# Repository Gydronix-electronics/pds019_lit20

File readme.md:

# PDS019_lit20

В этом репозитории содержатся исходники устройства PDS019_lit20.

Конструктивно устройство представляет из себя две печатные платы, размещенные в корпусе для монтажа на DIN-рейку [GAINTA D3MG](https://www.gainta.com/en/d3mg.html)

# Внешний вид платы А (верхней платы)

# Внешний вид платы B (нижней платы)

3d модель для онлайн просмотра доступна [по ссылке](https://a360.co/4tmWj8G)

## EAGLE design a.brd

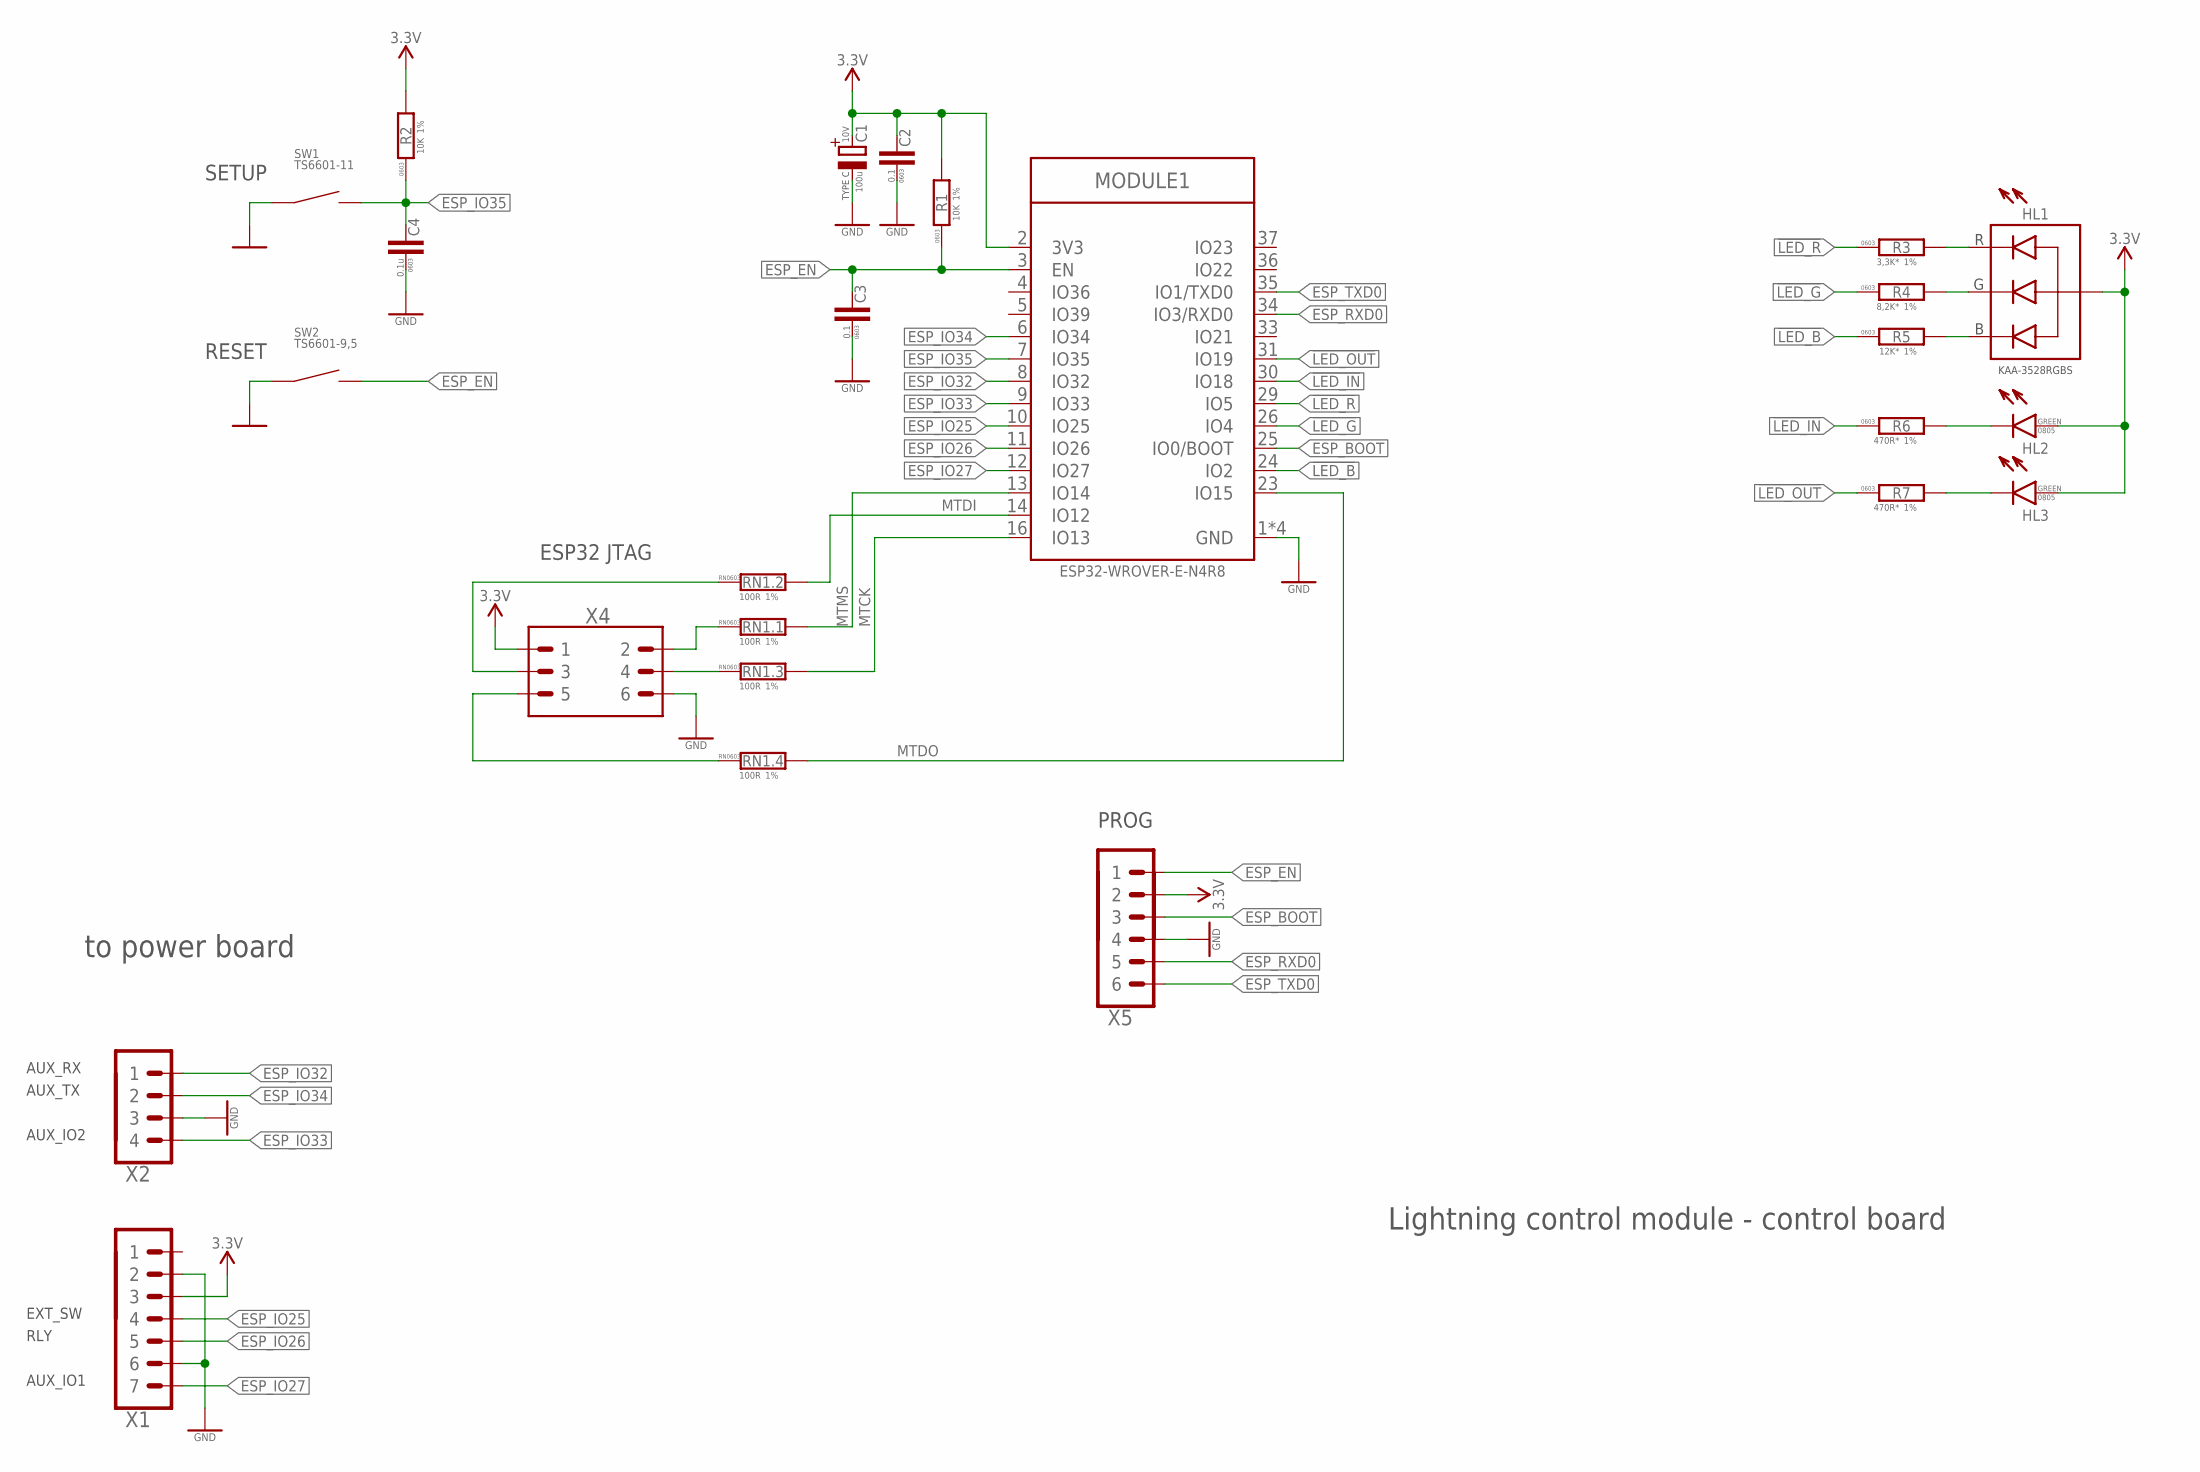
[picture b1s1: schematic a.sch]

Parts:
C1: 100u; CTANT_TYPE_C; VOLTAGE 10V
C2, C3: 0.1; C0603
C4: 0.1u; C0603
HL1: LED_RGB-KAA-3528RGBS; LED3528
HL2, HL3: LED-0805; LED0805
MODULE1: ESP32-WROVER-(I)E; ESP32-WROVER-E
R1, R2: 10K; R0603
R3: 3,3K*; R0603
R4: 8,2K*; R0603
R5: 12K*; R0603
R6, R7: 470R*; R0603
RN1: 100R; R_4X0603
SW1: TS6601-11; SW4-6.0X6.0X5.0MM
SW2: TS6601-9,5; SW4-6.0X6.0X5.0MM
X1: PINHEAD_1X07-2.54; 1X07-PTH-2.54
X2: PINHEAD_1X04-2.54; 1X04-PTH-2.54
X4: PINHEAD_2X03-PTH-2.54; 2X03-PTH-2.54
X5: PINHEAD_1X06-2-MALE; 1X06-PTH-2

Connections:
!LED_B: MODULE1.24 (IO2), R5.1
!LED_G: MODULE1.26 (IO4), R4.1
!LED_IN: MODULE1.30 (IO18), R6.1
!LED_OUT: MODULE1.31 (IO19), R7.1
!LED_R: MODULE1.29 (IO5), R3.1
ESP_BOOT: MODULE1.25 (IO0/BOOT), X5.3
ESP_EN: C3.2, MODULE1.3 (EN), R1.1, SW2.2, SW2.3 (2), X5.1
ESP_IO25: MODULE1.10 (IO25), X1.4
ESP_IO26: MODULE1.11 (IO26), X1.5
ESP_IO27: MODULE1.12 (IO27), X1.7
ESP_IO32: MODULE1.8 (IO32), X2.1
ESP_IO33: MODULE1.9 (IO33), X2.4
ESP_IO34: MODULE1.6 (IO34), X2.2
ESP_IO35: C4.2, MODULE1.7 (IO35), R2.1, SW1.2, SW1.3 (2)
ESP_RXD0: MODULE1.34 (IO3/RXD0), X5.5
ESP_TXD0: MODULE1.35 (IO1/TXD0), X5.6
GND: C1.-, C2.1, C3.1, C4.1, MODULE1.1 (GND), MODULE1.15 (GND), MODULE1.38 (GND), MODULE1.39 (GND), SW1.1, SW1.4 (1), SW2.1, SW2.4 (1), X1.2, X1.6, X2.3, X4.6, X5.4
MTCK: MODULE1.16 (IO13), RN1.6 (2)
MTDI: MODULE1.14 (IO12), RN1.7 (2)
MTDO: MODULE1.23 (IO15), RN1.5 (2)
MTMS: MODULE1.13 (IO14), RN1.8 (2)
unnamed: HL1.4 (B), R5.2
unnamed: HL1.3 (G), R4.2
unnamed: HL1.1 (R), R3.2
unnamed: HL2.C, R6.2
unnamed: HL3.C, R7.2
unnamed: RN1.4 (1), X4.5
unnamed: RN1.1, X4.2
unnamed: RN1.2 (1), X4.3
unnamed: RN1.3 (1), X4.4
VDD_3V3: C1.+, C2.2, HL1.2 (A), HL2.A, HL3.A, MODULE1.2 (3V3), R1.2, R2.2, X1.3, X4.1, X5.2

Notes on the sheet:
ESP32 JTAG
RESET
SETUP
PROG
to power board
AUX_RX
AUX_TX
AUX_IO2
EXT_SW
RLY
AUX_IO1
Lightning control module - control board

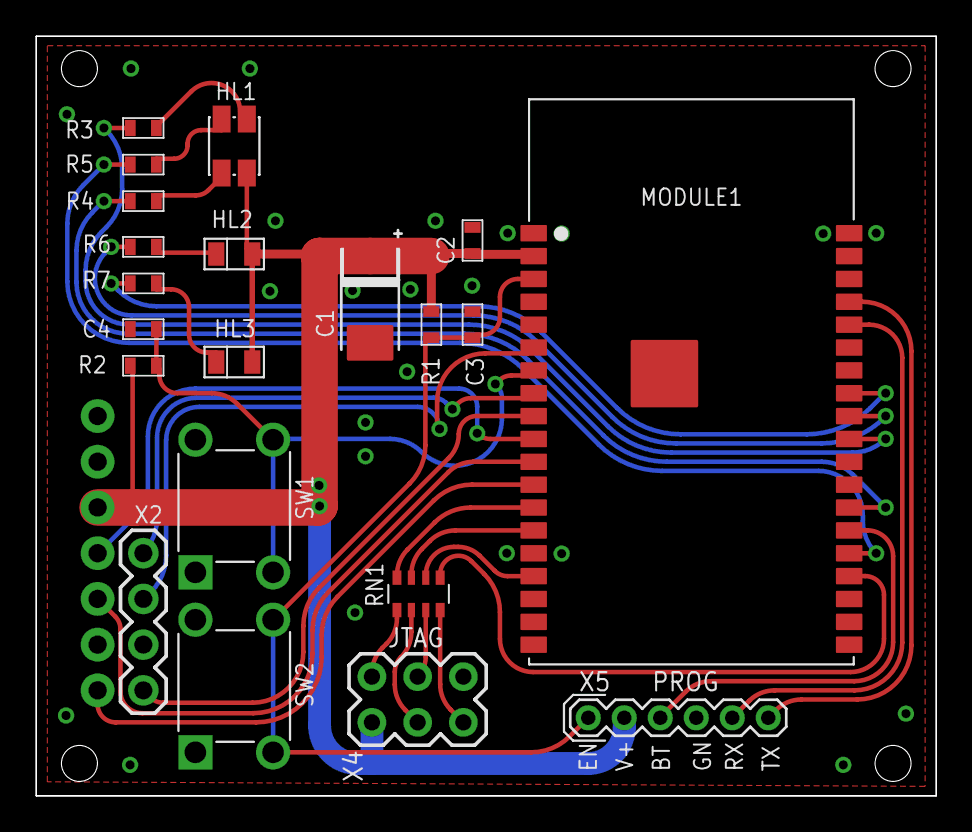
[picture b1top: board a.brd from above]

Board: 2 copper layers, 50.0 x 42.2 mm, 23 parts (1 on the bottom side), 31 nets.

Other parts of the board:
U$2: D3MG_PCB_UP

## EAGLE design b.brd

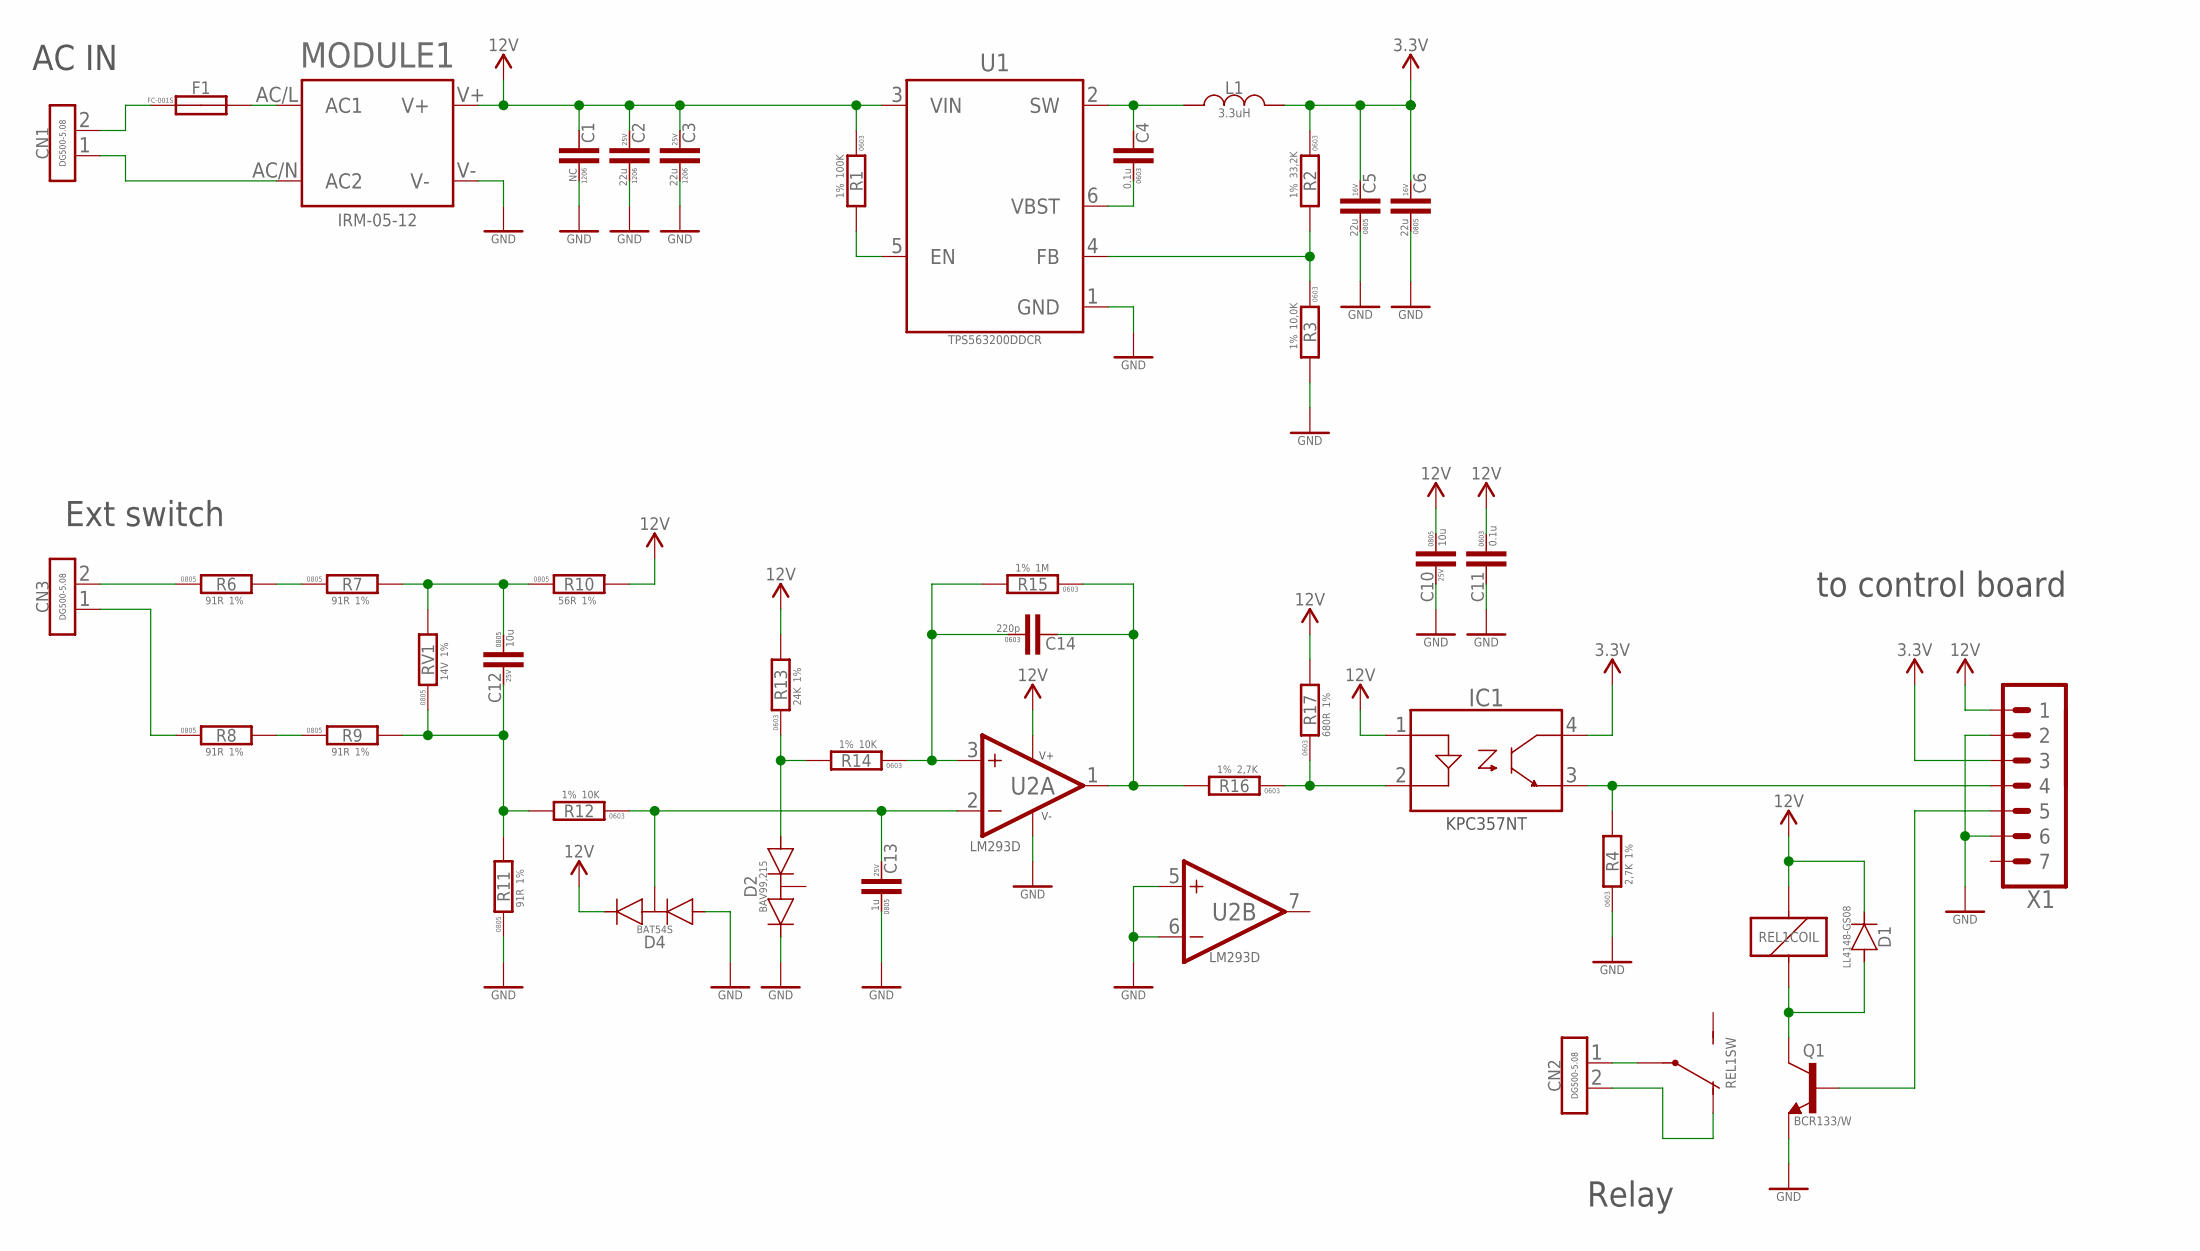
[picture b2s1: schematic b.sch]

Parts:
C1: NC; C1206
C2, C3: 22u; C1206; VOLTAGE 25V
C4, C11: 0.1u; C0603
C5, C6: 22u; C0805; VOLTAGE 16V
C10, C12: 10u; C0805; VOLTAGE 25V
C13: 1u; C0805; VOLTAGE 25V
C14: 220p; C0603
CN1, CN3: DG508V-2P; DG500-5.08-02P
CN2: CON-2P-DG500-5.08; DG500-5.08-02P
D1: LL4148; LL-34
D2: BAV99-SOT23; SOT23
D4: BAT54S-SOT23; SOT23
F1: 2A; FC-001S
IC1: KPC357NT-SOP-4; -SOP-4
L1: 3.3uH; LSMD_05020
MODULE1: IRM-05-12; IRM-05
Q1: BCR133; SOT23B-3
R1: 100K; R0603
R2: 33,2K; R0603
R3: 10,0K; R0603
R4, R16: 2,7K; R0603
R6, R7, R8, R9, R11: 91R; R0805
R10: 56R; R0805
R12, R14: 10K; R0603
R13: 24K; R0603
R15: 1M; R0603
R17: 680R; R0603
REL1: RELAY_SPDTHJR-3FF-SH; HJR-3FF-12VDC-S-Z
RV1: 14V; R0805
U1: TPS563200; SOT23-6
U2: LM293D; SOIC8
X1: PINHEAD_1X07-2.54; 1X07-PTH-2.54

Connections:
EXT_SW: IC1.3 (EMITTER), R4.2, X1.4
GND: C1.P$1 (1), C2.P$1 (1), C3.P$1 (1), C5.1, C6.1, C10.2, C11.2, C13.1, D2.2 (C), D4.1 (A), MODULE1.V-, Q1.2 (E), R3.2, R4.1, R11.1, U1.1 (GND), U2.4 (V-), U2.5 (IN+), U2.6 (IN-), X1.2, X1.6
unnamed: D1.A, Q1.3 (C), REL1.2 (1)
unnamed: Q1.1 (B), X1.5
unnamed: CN2.1, REL1.1 (COM)
unnamed: CN1.1, MODULE1.AC/N (AC2)
unnamed: CN1.2, F1.1-1 (1), F1.1-2 (1)
unnamed: F1.2-1 (2), F1.2-2 (2), MODULE1.AC/L (AC1)
unnamed: CN2.2, REL1.4 (NC)
unnamed: R2.2, R3.1, U1.4 (FB)
unnamed: CN3.2, R6.1
unnamed: CN3.1, R8.1
unnamed: R1.2, U1.5 (EN)
unnamed: C4.1, U1.6 (VBST)
unnamed: C4.2, L1.1, U1.2 (SW)
unnamed: IC1.2 (C), R16.1, R17.1
unnamed: C14.2, R15.1, R16.2, U2.1 (OUT)
unnamed: C13.2, D4.3 (COMMON), R12.1, U2.2 (IN-)
unnamed: C12.1, R7.2, R10.1, RV1.2
unnamed: R6.2, R7.1
unnamed: R8.2, R9.1
unnamed: C14.1, R14.1, R15.2, U2.3 (IN+)
unnamed: D2.1 (A), R13.1, R14.2
unnamed: C12.2, R9.2, R11.2, R12.2, RV1.1
VDD_3V3: C5.2, C6.2, IC1.4 (COLLECTOR), L1.2, R2.1, X1.3
VDD_12V: C1.P$2 (2), C2.P$2 (2), C3.P$2 (2), C10.1, C11.1, D1.C, D4.2 (C), IC1.1 (A), MODULE1.V+, R1.1, R10.2, R13.2, R17.2, REL1.5 (2), U1.3 (VIN), U2.8 (V+), X1.1

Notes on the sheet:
Ext switch
AC IN
Relay
to control board

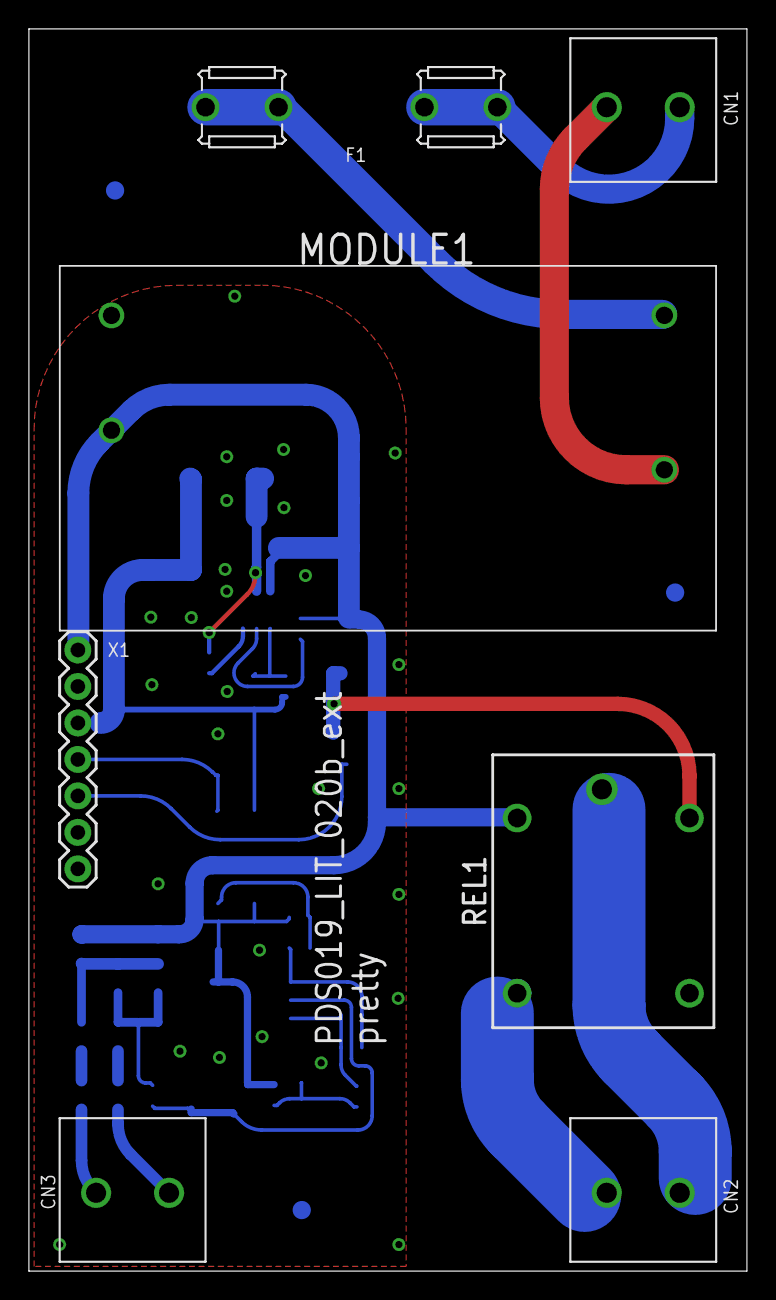
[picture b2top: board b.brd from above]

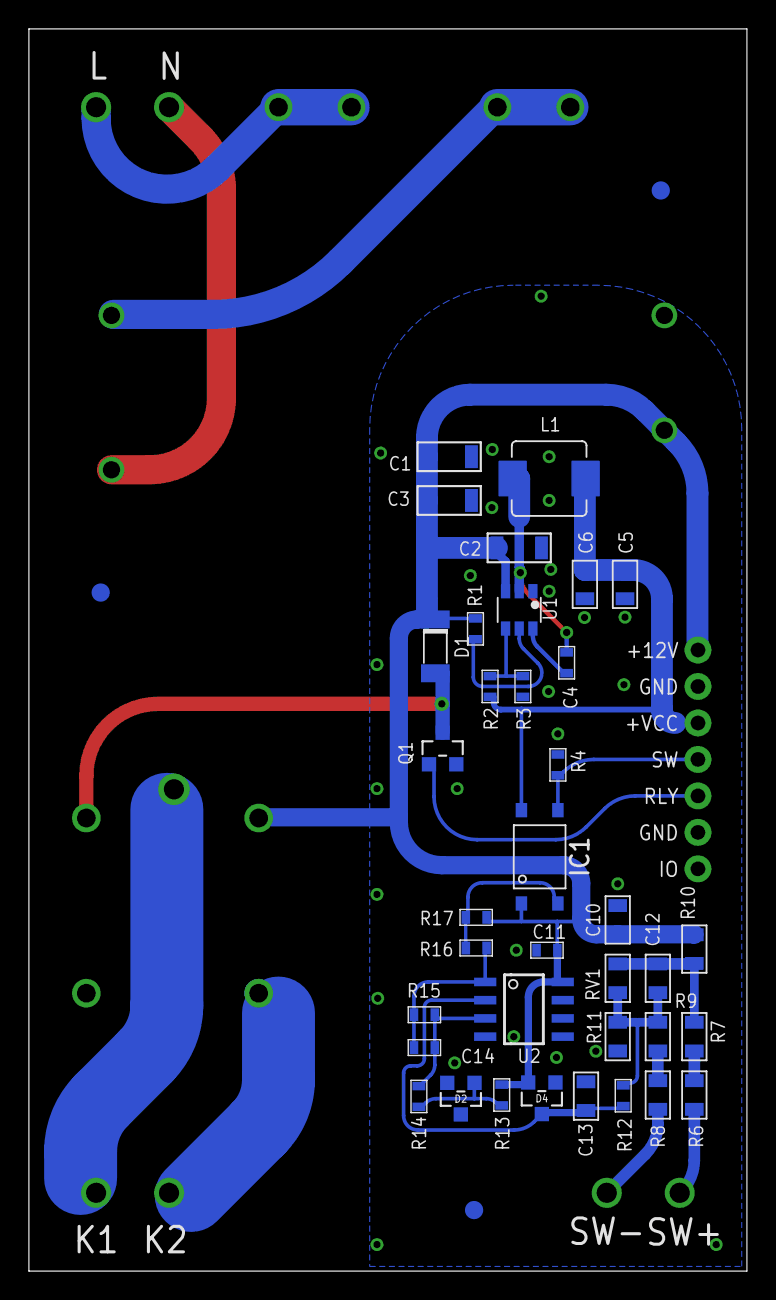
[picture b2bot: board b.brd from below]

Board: 2 copper layers, 50.0 x 86.5 mm, 47 parts (39 on the bottom side), 26 nets.

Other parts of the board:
PCB_B: D3MG_PCB
U$1, U$2, U$3: REF_POINT_D1.27_D3.81

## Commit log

2026-04-01 initial import
2026-04-01 readme
2026-04-01 more import
2026-04-02 A pcb updated
2026-04-02 Import
2026-04-02 Libraries update
